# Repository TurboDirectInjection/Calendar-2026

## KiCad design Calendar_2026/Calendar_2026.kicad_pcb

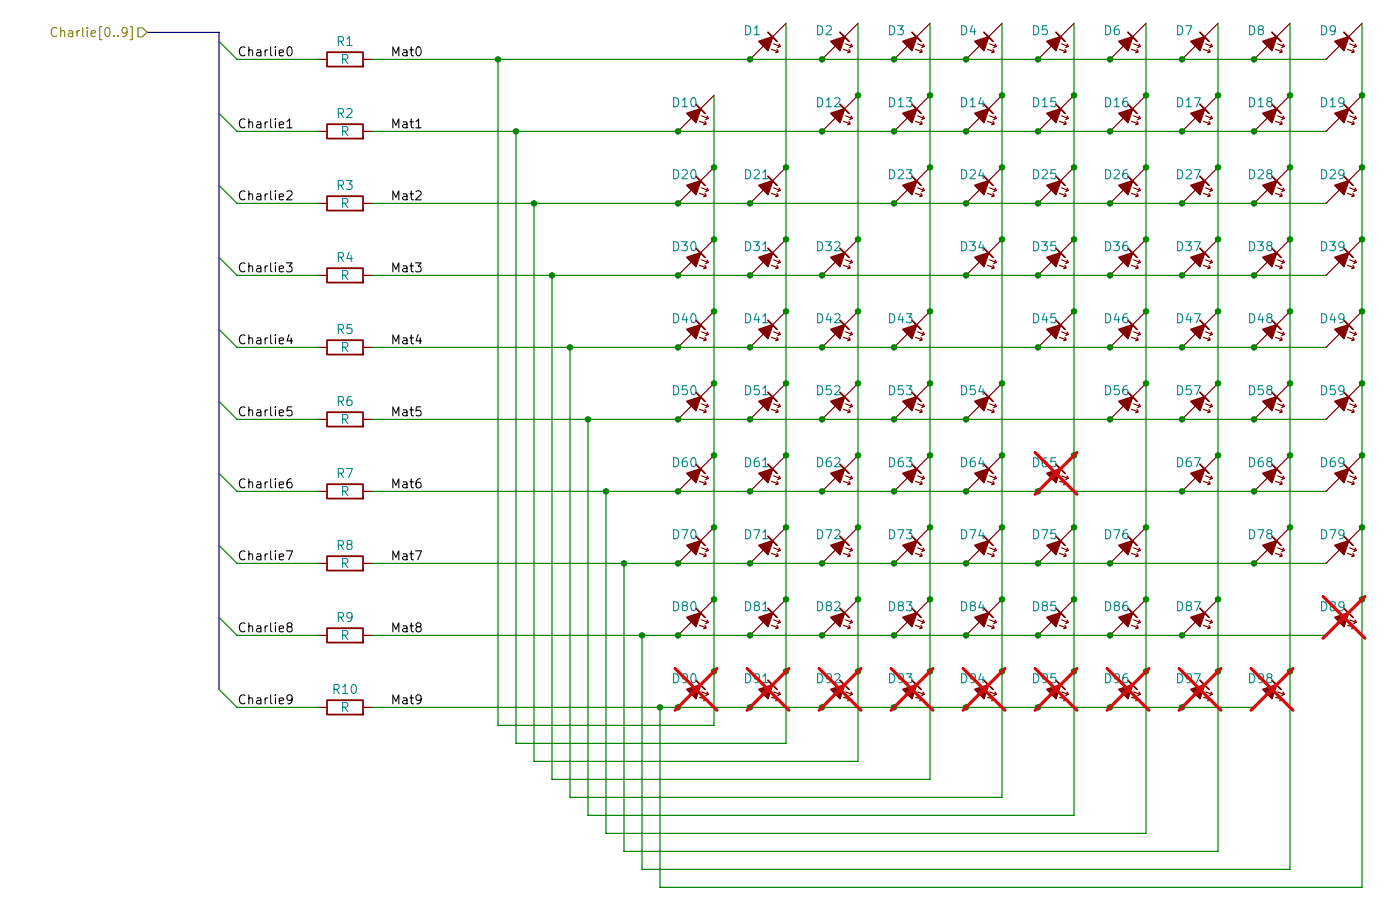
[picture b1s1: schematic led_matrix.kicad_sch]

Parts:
D1, D2, D3, D4, D5, D6, D7, D8, D9, D10, D12, D13, D14, D15, D16, D17, D18, D19, D20, D21, D23, D24, D25, D26, D27, D28, D29, D30, D31, D32, D34, D35, D36, D37, D38, D39, D40, D41, D42, D43, D45, D46, D47, D48, D49, D50, D51, D52, D53, D54, D56, D57, D58, D59, D60, D61, D62, D63, D64, D67, D68, D69, D70, D71, D72, D73, D74, D75, D76, D78, D79, D80, D81, D82, D83, D84, D85, D86, D87: LED; LED_0603_1608Metric
D65, D89, D90, D91, D92, D93, D94, D95, D96, D97, D98: LED; LED_0603_1608Metric; not fitted
R1, R2, R3, R4, R5, R6, R7, R8, R9, R10: R; R_0603_1608Metric

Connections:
/LED Matrix/Charlie0: R1.1; also elsewhere on the board
/LED Matrix/Charlie1: R2.1; also elsewhere on the board
/LED Matrix/Charlie2: R3.1; also elsewhere on the board
/LED Matrix/Charlie3: R4.1; also elsewhere on the board
/LED Matrix/Charlie4: R5.1; also elsewhere on the board
/LED Matrix/Charlie5: R6.1; also elsewhere on the board
/LED Matrix/Charlie6: R7.1; also elsewhere on the board
/LED Matrix/Charlie7: R8.1; also elsewhere on the board
/LED Matrix/Charlie8: R9.1; also elsewhere on the board
/LED Matrix/Charlie9: R10.1; also elsewhere on the board
/LED Matrix/Mat0: D1.2 (A), D2.2 (A), D3.2 (A), D4.2 (A), D5.2 (A), D6.2 (A), D7.2 (A), D8.2 (A), D9.2 (A), D10.1 (K), D20.1 (K), D30.1 (K), D40.1 (K), D50.1 (K), D60.1 (K), D70.1 (K), D80.1 (K), D90.1 (K), R1.2
/LED Matrix/Mat1: D1.1 (K), D10.2 (A), D12.2 (A), D13.2 (A), D14.2 (A), D15.2 (A), D16.2 (A), D17.2 (A), D18.2 (A), D19.2 (A), D21.1 (K), D31.1 (K), D41.1 (K), D51.1 (K), D61.1 (K), D71.1 (K), D81.1 (K), D91.1 (K), R2.2
/LED Matrix/Mat2: D2.1 (K), D12.1 (K), D20.2 (A), D21.2 (A), D23.2 (A), D24.2 (A), D25.2 (A), D26.2 (A), D27.2 (A), D28.2 (A), D29.2 (A), D32.1 (K), D42.1 (K), D52.1 (K), D62.1 (K), D72.1 (K), D82.1 (K), D92.1 (K), R3.2
/LED Matrix/Mat3: D3.1 (K), D13.1 (K), D23.1 (K), D30.2 (A), D31.2 (A), D32.2 (A), D34.2 (A), D35.2 (A), D36.2 (A), D37.2 (A), D38.2 (A), D39.2 (A), D43.1 (K), D53.1 (K), D63.1 (K), D73.1 (K), D83.1 (K), D93.1 (K), R4.2
/LED Matrix/Mat4: D4.1 (K), D14.1 (K), D24.1 (K), D34.1 (K), D40.2 (A), D41.2 (A), D42.2 (A), D43.2 (A), D45.2 (A), D46.2 (A), D47.2 (A), D48.2 (A), D49.2 (A), D54.1 (K), D64.1 (K), D74.1 (K), D84.1 (K), D94.1 (K), R5.2
/LED Matrix/Mat5: D5.1 (K), D15.1 (K), D25.1 (K), D35.1 (K), D45.1 (K), D50.2 (A), D51.2 (A), D52.2 (A), D53.2 (A), D54.2 (A), D56.2 (A), D57.2 (A), D58.2 (A), D59.2 (A), D65.1 (K), D75.1 (K), D85.1 (K), D95.1 (K), R6.2
/LED Matrix/Mat6: D6.1 (K), D16.1 (K), D26.1 (K), D36.1 (K), D46.1 (K), D56.1 (K), D60.2 (A), D61.2 (A), D62.2 (A), D63.2 (A), D64.2 (A), D65.2 (A), D67.2 (A), D68.2 (A), D69.2 (A), D76.1 (K), D86.1 (K), D96.1 (K), R7.2
/LED Matrix/Mat7: D7.1 (K), D17.1 (K), D27.1 (K), D37.1 (K), D47.1 (K), D57.1 (K), D67.1 (K), D70.2 (A), D71.2 (A), D72.2 (A), D73.2 (A), D74.2 (A), D75.2 (A), D76.2 (A), D78.2 (A), D79.2 (A), D87.1 (K), D97.1 (K), R8.2
/LED Matrix/Mat8: D8.1 (K), D18.1 (K), D28.1 (K), D38.1 (K), D48.1 (K), D58.1 (K), D68.1 (K), D78.1 (K), D80.2 (A), D81.2 (A), D82.2 (A), D83.2 (A), D84.2 (A), D85.2 (A), D86.2 (A), D87.2 (A), D89.2 (A), D98.1 (K), R9.2
/LED Matrix/Mat9: D9.1 (K), D19.1 (K), D29.1 (K), D39.1 (K), D49.1 (K), D59.1 (K), D69.1 (K), D79.1 (K), D89.1 (K), D90.2 (A), D91.2 (A), D92.2 (A), D93.2 (A), D94.2 (A), D95.2 (A), D96.2 (A), D97.2 (A), D98.2 (A), R10.2

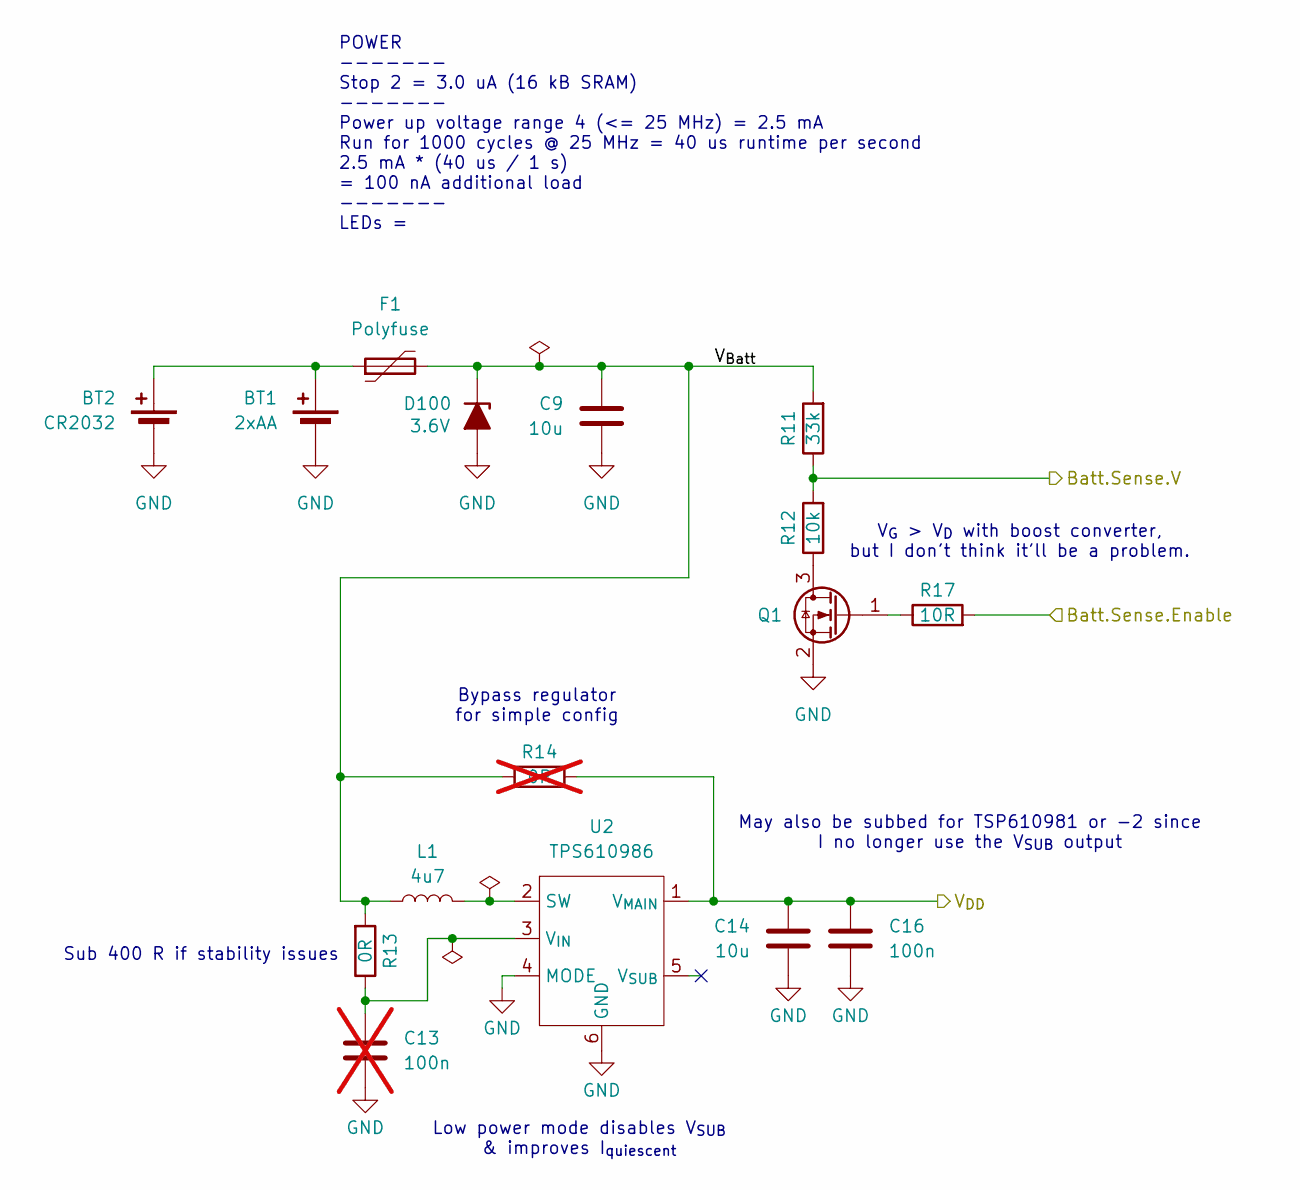
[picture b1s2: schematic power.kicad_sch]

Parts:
BT1: 2xAA; BatteryHolder_Keystone_2462_2xAA
BT2: CR2032; BAT-HLD-001
C9, C14: 10u; C_1210_3225Metric
C13: 100n; C_0402_1005Metric; not fitted
C16: 100n; C_0402_1005Metric
D100: TVS; D_SOD-323_HandSoldering
F1: Polyfuse; Fuse_1210_3225Metric_Pad1.42x2.65mm_HandSolder
L1: 4u7; L_1210_3225Metric
Q1: Q_NMOS_GSD; SOT-23
R11: 33k; R_0603_1608Metric
R12: 10k; R_0603_1608Metric
R13: 0R; R_0603_1608Metric
R14: 0R; R_0603_1608Metric; not fitted
R17: 10R; R_0603_1608Metric
U2: TPS610986; WSON-6_1.5x1.5mm_P0.5mm

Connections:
/Power/Batt.Sense.Enable: R17.2; also elsewhere on the board
/Power/Batt.Sense.V: R11.1, R12.2; also elsewhere on the board
/Power/V_{Batt}: C9.1, D100.1 (K), F1.2, L1.1, R11.2, R13.2, R14.1
GND: BT1.2 (-), BT2.2 (-), C9.2, C13.2, C14.2, C16.2, D100.2 (A), Q1.2 (S), U2.4 (MODE), U2.6 (GND); also elsewhere on the board
unnamed: BT1.1 (+), BT2.1 (+), F1.1
unnamed: Q1.3 (D), R12.1
unnamed: Q1.1 (G), R17.1
unnamed: L1.2, U2.2 (SW)
unnamed: C13.1, R13.1, U2.3 (V_{IN})
VDD: C14.1, C16.1, R14.2, U2.1 (V_{MAIN}); also elsewhere on the board

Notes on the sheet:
Low power mode disables V_{SUB} & improves I_{quiescent}
Bypass regulator for simple config
May also be subbed for TSP610981 or -2 since I no longer use the V_{SUB} output
POWER ------- Stop 2 = 3.0 uA (16 kB SRAM) ------- Power up voltage range 4 (<= 25 MHz) = 2.5 mA Run for 1000 cycles @ 25 MHz = 40 us runtime per second 2.5 mA * (40 us / 1 s) = 100 nA additional load ------- LEDs =
Sub 400 R if stability issues
V_{G} > V_{D} with boost converter, but I don't think it'll be a problem.

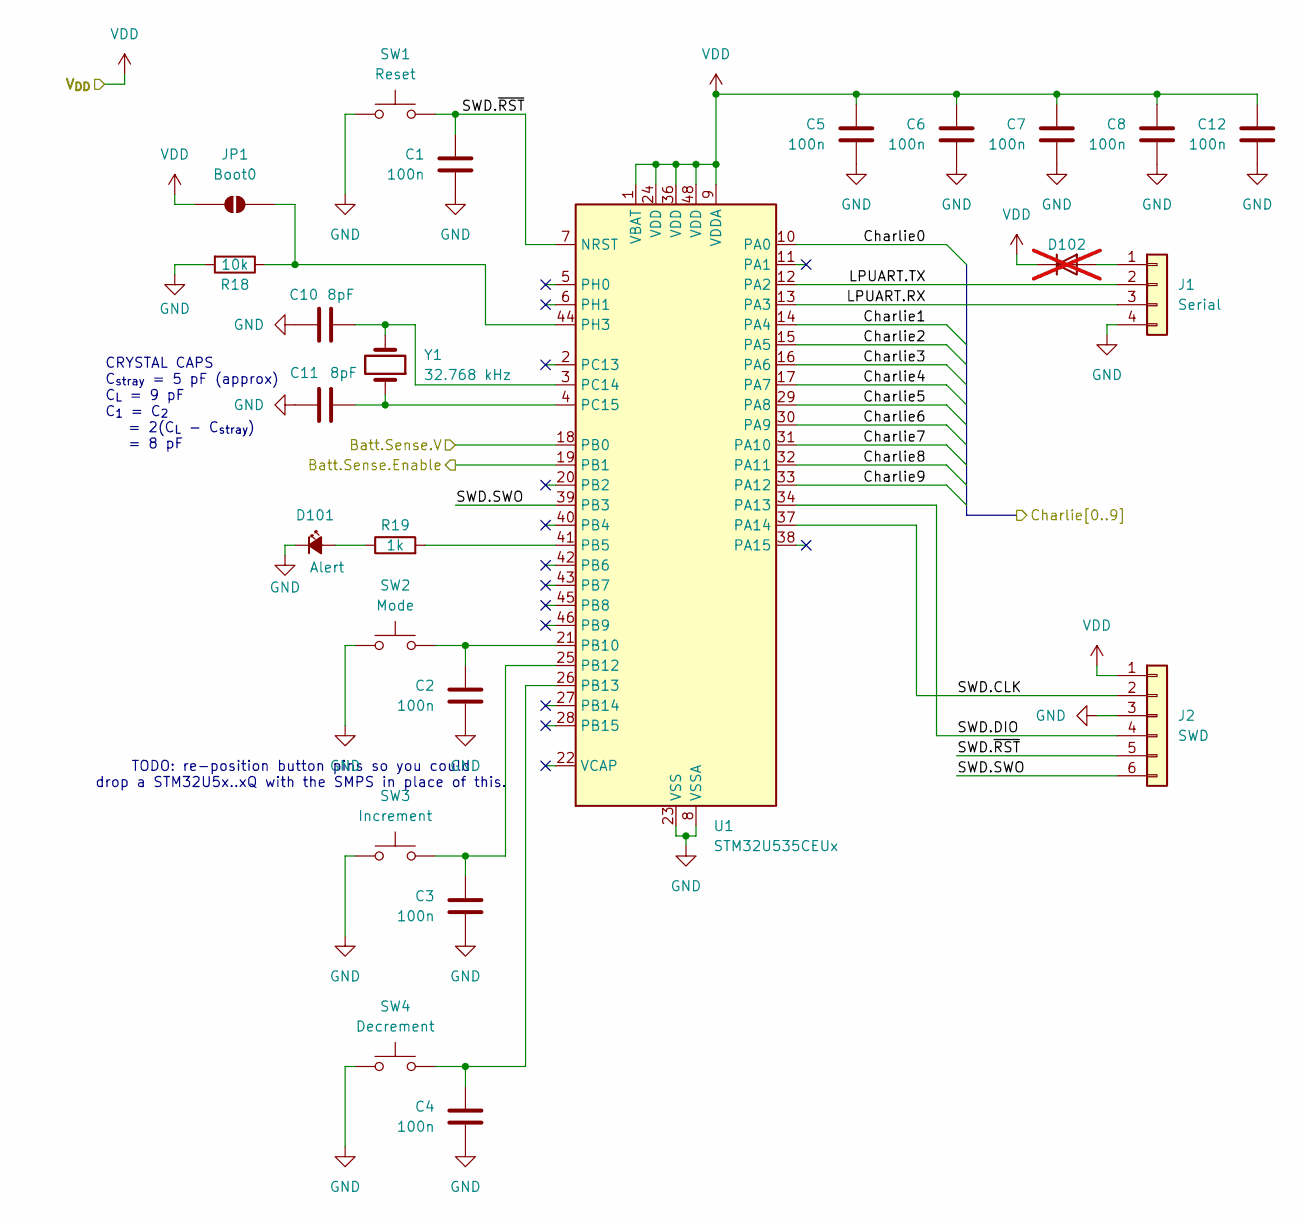
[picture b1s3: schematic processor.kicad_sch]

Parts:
C1, C2, C3, C4, C5, C6, C7, C8, C12: 100n; C_0402_1005Metric
C10, C11: 8pF; C_0603_1608Metric
D101: Alert; LED_0603_1608Metric
D102: D; D_SOD-323_HandSoldering; not fitted
J1: Serial; JST_SH_BM04B-SRSS-TB_1x04-1MP_P1.00mm_Vertical
J2: SWD; JST_SH_BM06B-SRSS-TB_1x06-1MP_P1.00mm_Vertical
JP1: Boot0; SolderJumper-2_P1.3mm_Open_RoundedPad1.0x1.5mm
R18: 10k; R_0603_1608Metric
R19: 1k; R_0603_1608Metric
SW1: Reset; Button_Switch_SMD_FSM2JSMAA
SW2: Mode; Button_Switch_SMD_FSM2JSMAA
SW3: Increment; Button_Switch_SMD_FSM2JSMAA
SW4: Decrement; Button_Switch_SMD_FSM2JSMAA
U1: STM32U535CEUx; QFN-48-1EP_7x7mm_P0.5mm_EP5.6x5.6mm
Y1: 32.768 kHz; 12.87001 Crystal

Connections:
/LED Matrix/Charlie0: U1.10 (PA0); also elsewhere on the board
/LED Matrix/Charlie1: U1.14 (PA4); also elsewhere on the board
/LED Matrix/Charlie2: U1.15 (PA5); also elsewhere on the board
/LED Matrix/Charlie3: U1.16 (PA6); also elsewhere on the board
/LED Matrix/Charlie4: U1.17 (PA7); also elsewhere on the board
/LED Matrix/Charlie5: U1.29 (PA8); also elsewhere on the board
/LED Matrix/Charlie6: U1.30 (PA9); also elsewhere on the board
/LED Matrix/Charlie7: U1.31 (PA10); also elsewhere on the board
/LED Matrix/Charlie8: U1.32 (PA11); also elsewhere on the board
/LED Matrix/Charlie9: U1.33 (PA12); also elsewhere on the board
/Power/Batt.Sense.Enable: U1.19 (PB1); also elsewhere on the board
/Power/Batt.Sense.V: U1.18 (PB0); also elsewhere on the board
/Processor/LPUART.RX: J1.3, U1.13 (PA3)
/Processor/LPUART.TX: J1.2, U1.12 (PA2)
/Processor/SWD.CLK: J2.2, U1.37 (PA14)
/Processor/SWD.DIO: J2.4, U1.34 (PA13)
/Processor/SWD.SWO: J2.6, U1.39 (PB3)
/Processor/SWD.~RST: C1.1, J2.5, SW1.2, U1.7 (NRST)
GND: C1.2, C2.2, C3.2, C4.2, C5.2, C6.2, C7.2, C8.2, C10.2, C11.1, C12.2, D101.1 (K), J1.4, J2.3, R18.2, SW1.1, SW2.1, SW3.1, SW4.1, U1.8 (VSSA), U1.23 (VSS), U1.35 (VSS), U1.47 (VSS), U1.49 (VSS); also elsewhere on the board
unnamed: D101.2 (A), R19.1
unnamed: D102.2 (A), J1.1
unnamed: JP1.2 (B), R18.1, U1.44 (PH3)
unnamed: R19.2, U1.41 (PB5)
unnamed: C2.1, SW2.2, U1.21 (PB10)
unnamed: C3.1, SW3.2, U1.25 (PB12)
unnamed: C4.1, SW4.2, U1.26 (PB13)
unnamed: C10.1, U1.3 (PC14), Y1.2
unnamed: C11.2, U1.4 (PC15), Y1.1
VDD: C5.1, C6.1, C7.1, C8.1, C12.1, D102.1 (K), J2.1, JP1.1 (A), U1.1 (VBAT), U1.9 (VDDA), U1.24 (VDD), U1.36 (VDD), U1.48 (VDD); also elsewhere on the board

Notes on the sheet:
TODO: re-position button pins so you could drop a STM32U5x..xQ with the SMPS in place of this.
CRYSTAL CAPS C_{stray} = 5 pF (approx) C_{L} = 9 pF C_{1} = C_{2} = 2(C_{L} - C_{stray}) = 8 pF

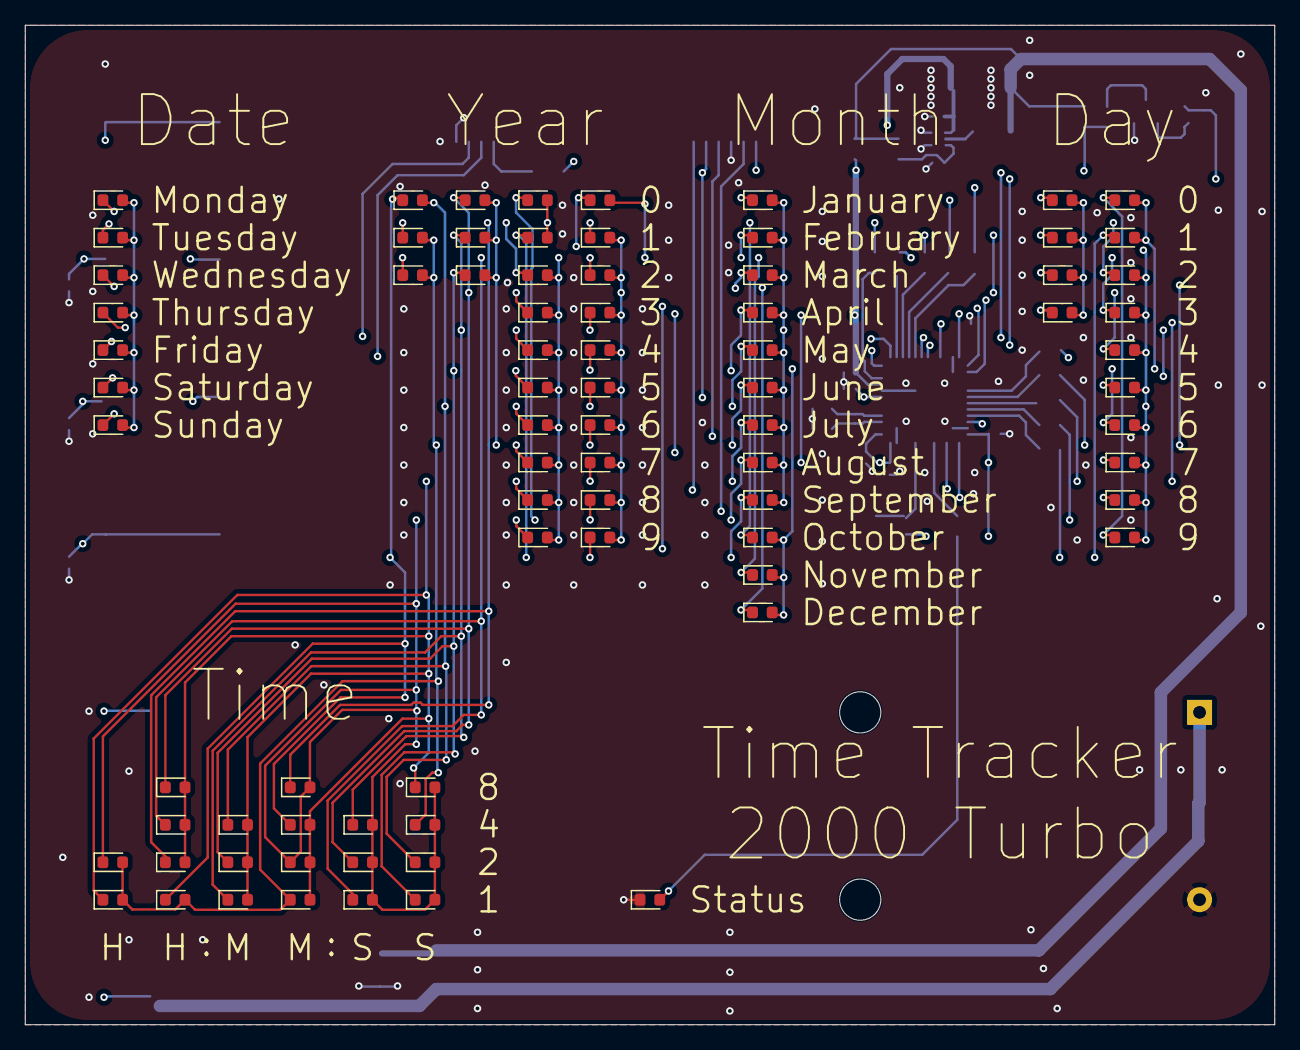
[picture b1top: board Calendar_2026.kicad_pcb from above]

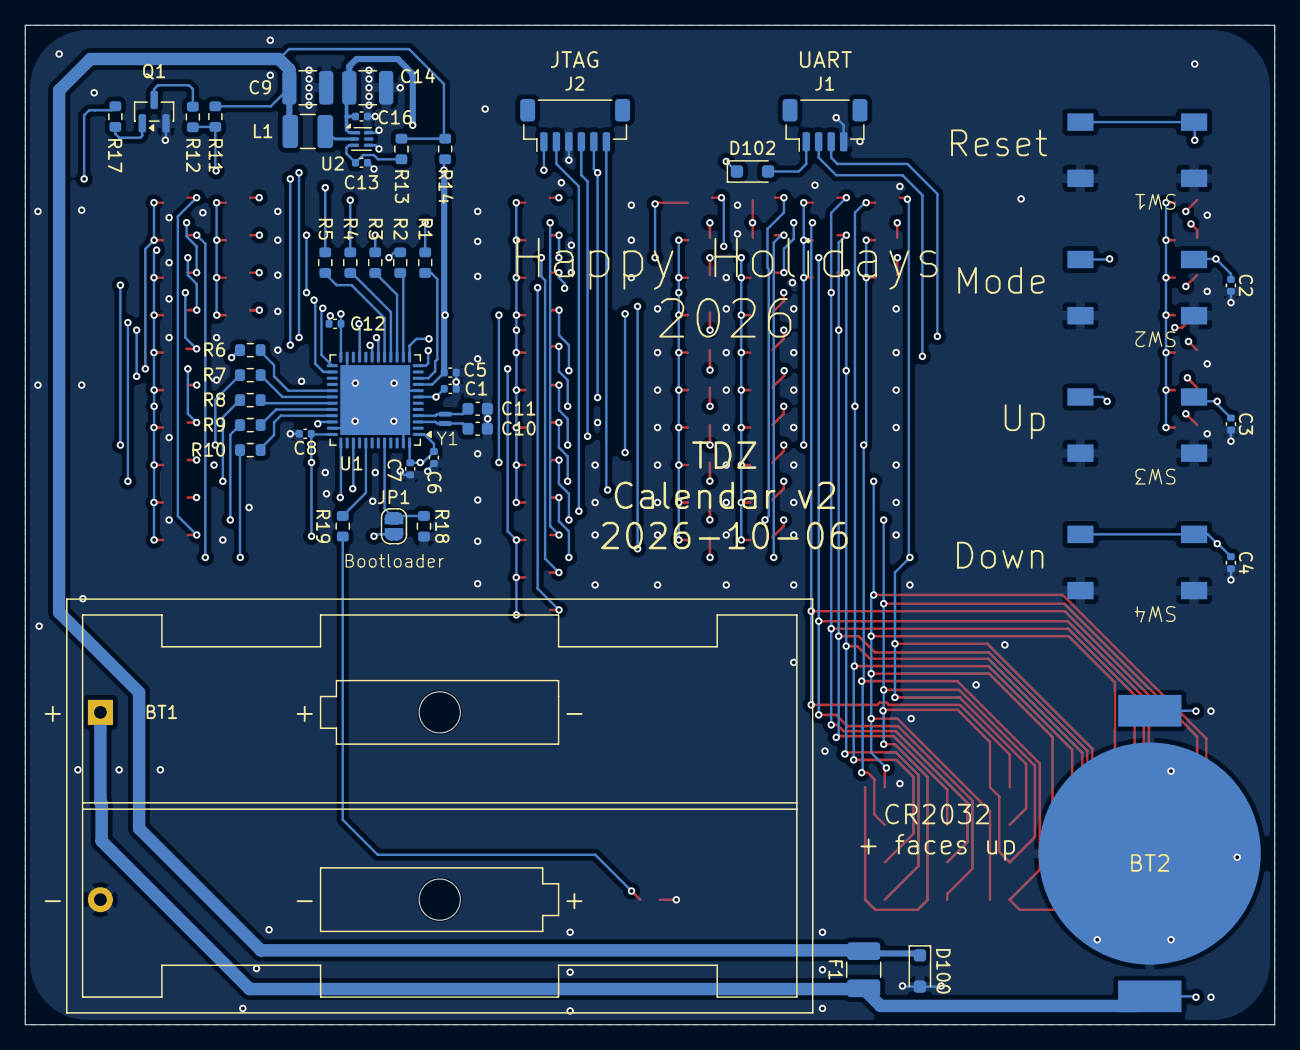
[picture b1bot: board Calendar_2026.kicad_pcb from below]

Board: 4 copper layers, 100.0 x 80.0 mm, 129 parts (49 on the bottom side), 45 nets.

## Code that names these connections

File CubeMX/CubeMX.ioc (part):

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Mcu.Name=STM32U535CBUx
Mcu.Package=UFQFPN48
Mcu.UserName=STM32U535CBUx
PA0.Signal=GPIO_Output
PA10.Signal=GPIO_Output
PA11.Signal=GPIO_Output
PA12.Signal=GPIO_Output
PA13\ (JTMS/SWDIO).Mode=Trace_Asynchronous_SW
PA13\ (JTMS/SWDIO).Signal=DEBUG_JTMS-SWDIO
PA14\ (JTCK/SWCLK).Mode=Trace_Asynchronous_SW
PA14\ (JTCK/SWCLK).Signal=DEBUG_JTCK-SWCLK
PA2.Mode=Asynchronous
PA2.Signal=LPUART1_TX
PA3.Mode=Asynchronous
PA3.Signal=LPUART1_RX
PA4.Signal=GPIO_Output
PA5.Signal=GPIO_Output
PA6.Signal=GPIO_Output
PA7.Signal=GPIO_Output
PA8.Signal=GPIO_Output
PA9.Signal=GPIO_Output
PB0.GPIOParameters=GPIO_Label
PB0.GPIO_Label=BATT_SENSE_V
PB0.Mode=IN15-Single-Ended
PB0.Signal=ADC1_IN15
PB1.GPIOParameters=GPIO_Label
PB1.GPIO_Label=BATT_SENSE_EN
PB1.Signal=GPIO_Output
PB10.GPIOParameters=GPIO_Label
PB10.GPIO_Label=SW_MODE
PB10.Signal=GPIO_Input
PB12.GPIOParameters=GPIO_Label
PB12.GPIO_Label=SW_UP
PB12.Signal=GPIO_Input
PB13.GPIOParameters=GPIO_Label
PB13.GPIO_Label=SW_DOWN
PB13.Signal=GPIO_Input
PB3\ (JTDO/TRACESWO).Mode=Trace_Asynchronous_SW
PB3\ (JTDO/TRACESWO).Signal=DEBUG_JTDO-SWO
PB5.GPIOParameters=GPIO_Label
PB5.GPIO_Label=LED_STATUS
PB5.Signal=GPIO_Output
PC14-OSC32_IN\ (PC14).Mode=LSE-External-Oscillator
PC14-OSC32_IN\ (PC14).Signal=RCC_OSC32_IN
PC15-OSC32_OUT\ (PC15).Mode=LSE-External-Oscillator
PC15-OSC32_OUT\ (PC15).Signal=RCC_OSC32_OUT
RCC.HSE_VALUE=16000000
board=custom
